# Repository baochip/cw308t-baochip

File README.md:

# Chipwhisperer 308 Target for Baochip

Design files for a chipwhisperer 308 target featuring the Baochip.

Contains a 400MHz bandwidth, 20x amplifier on IDD.

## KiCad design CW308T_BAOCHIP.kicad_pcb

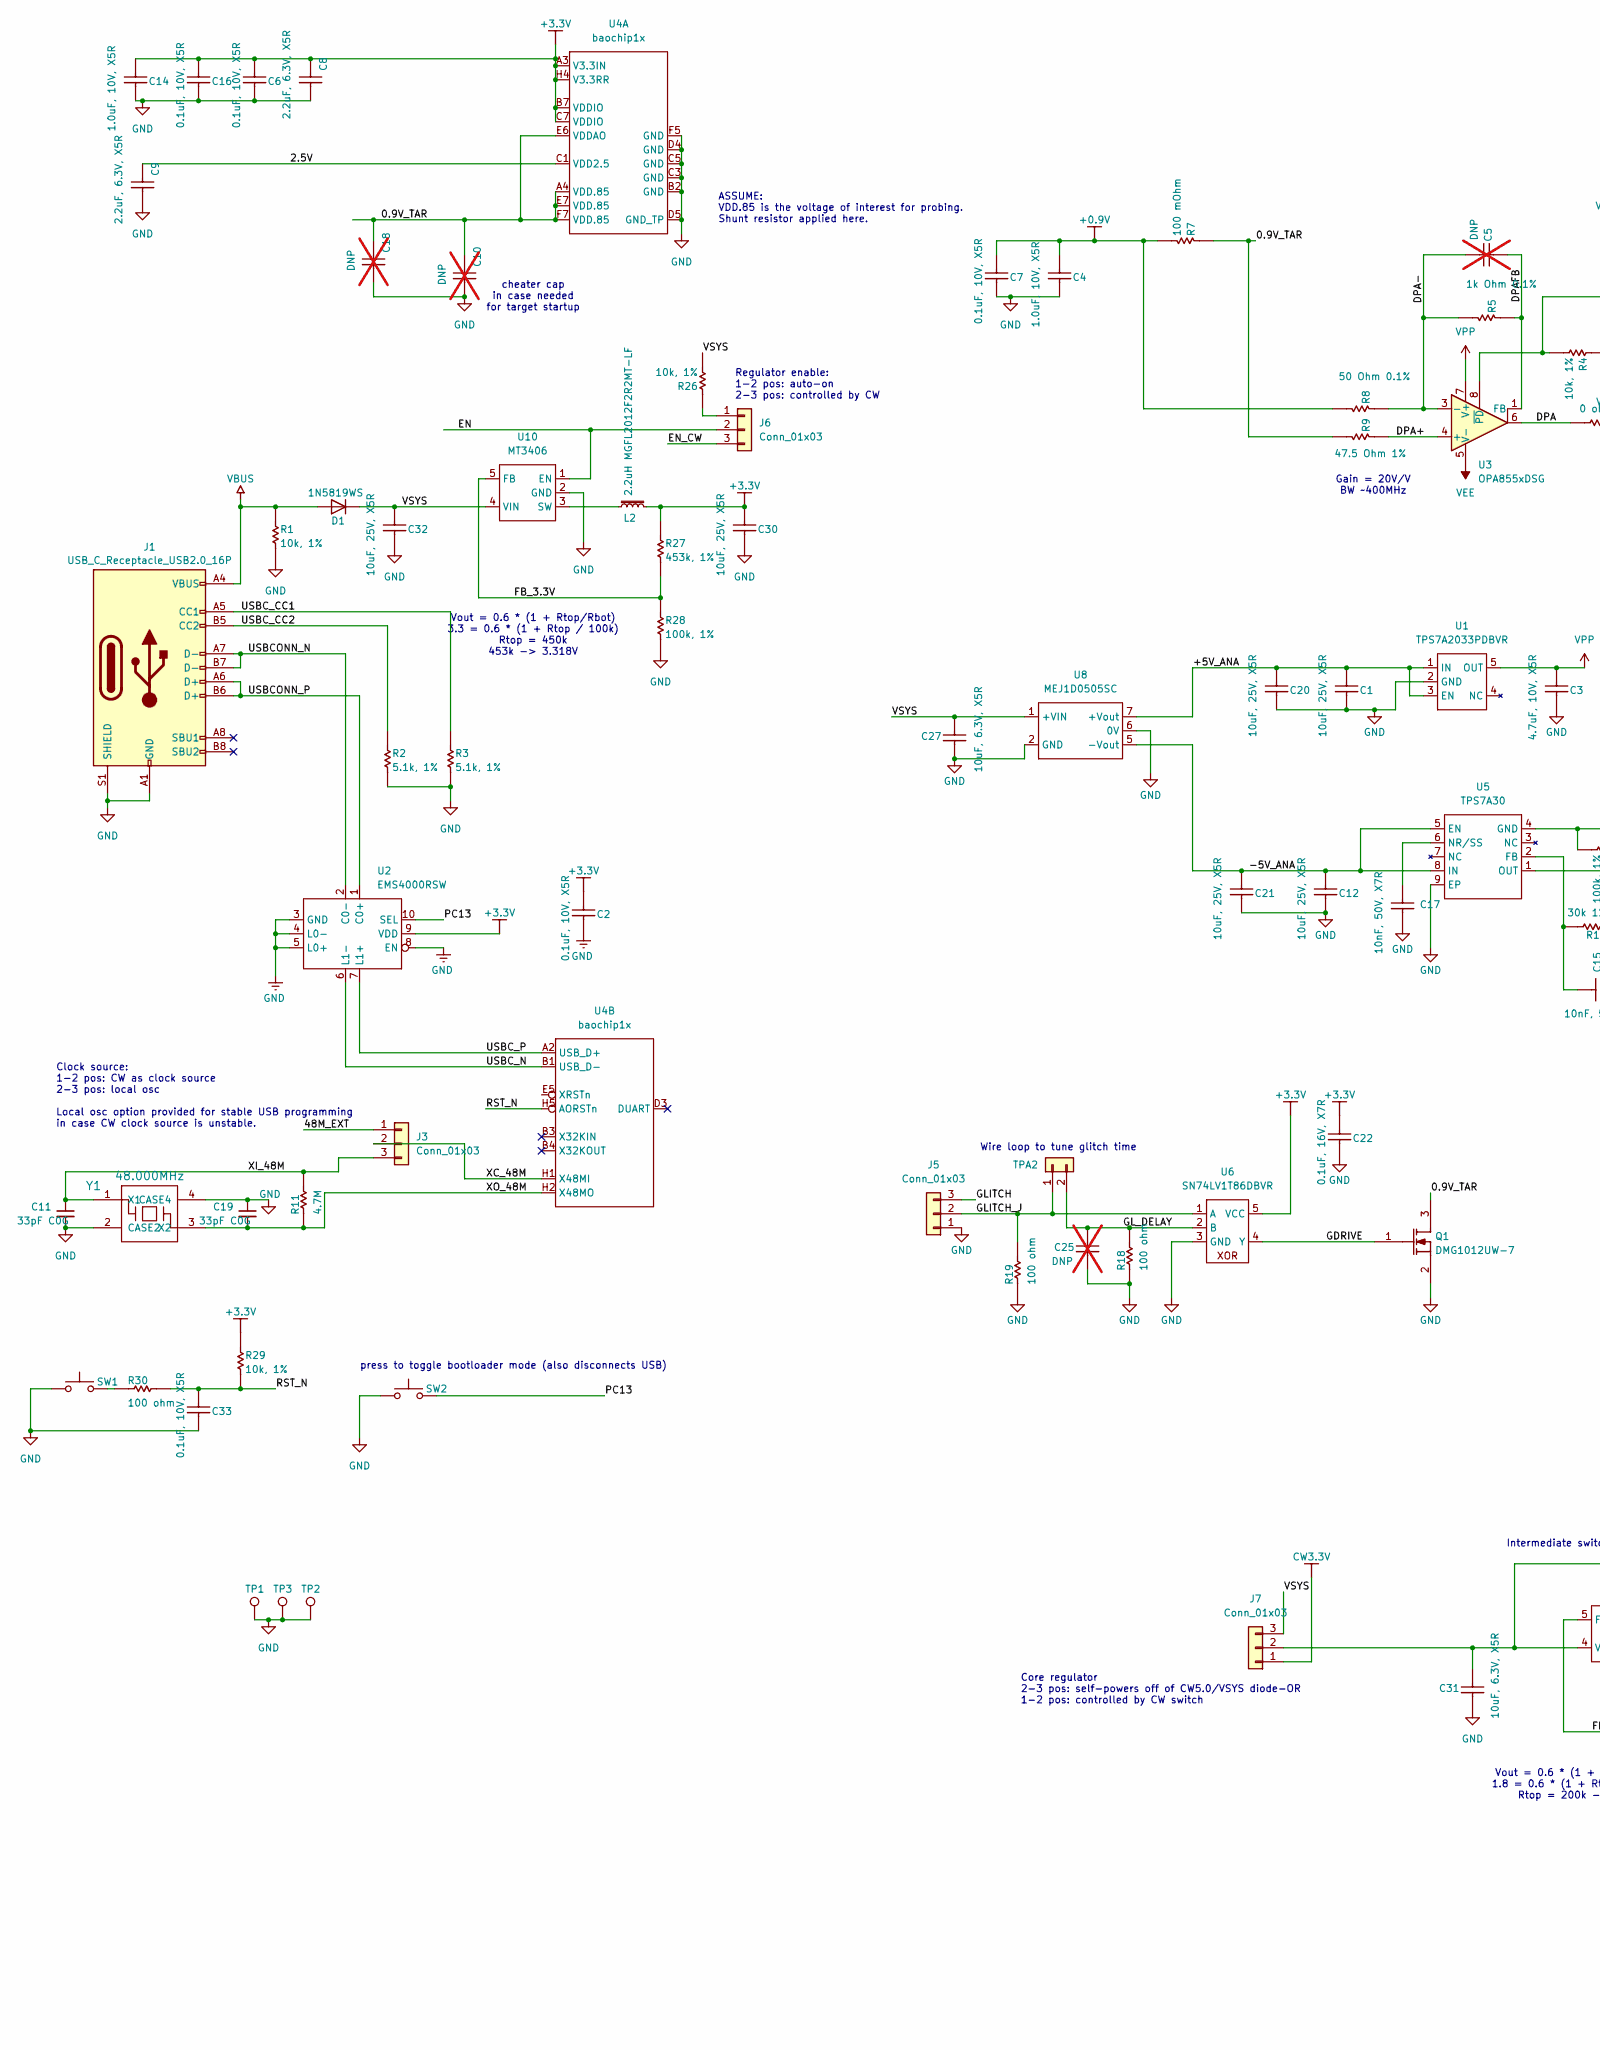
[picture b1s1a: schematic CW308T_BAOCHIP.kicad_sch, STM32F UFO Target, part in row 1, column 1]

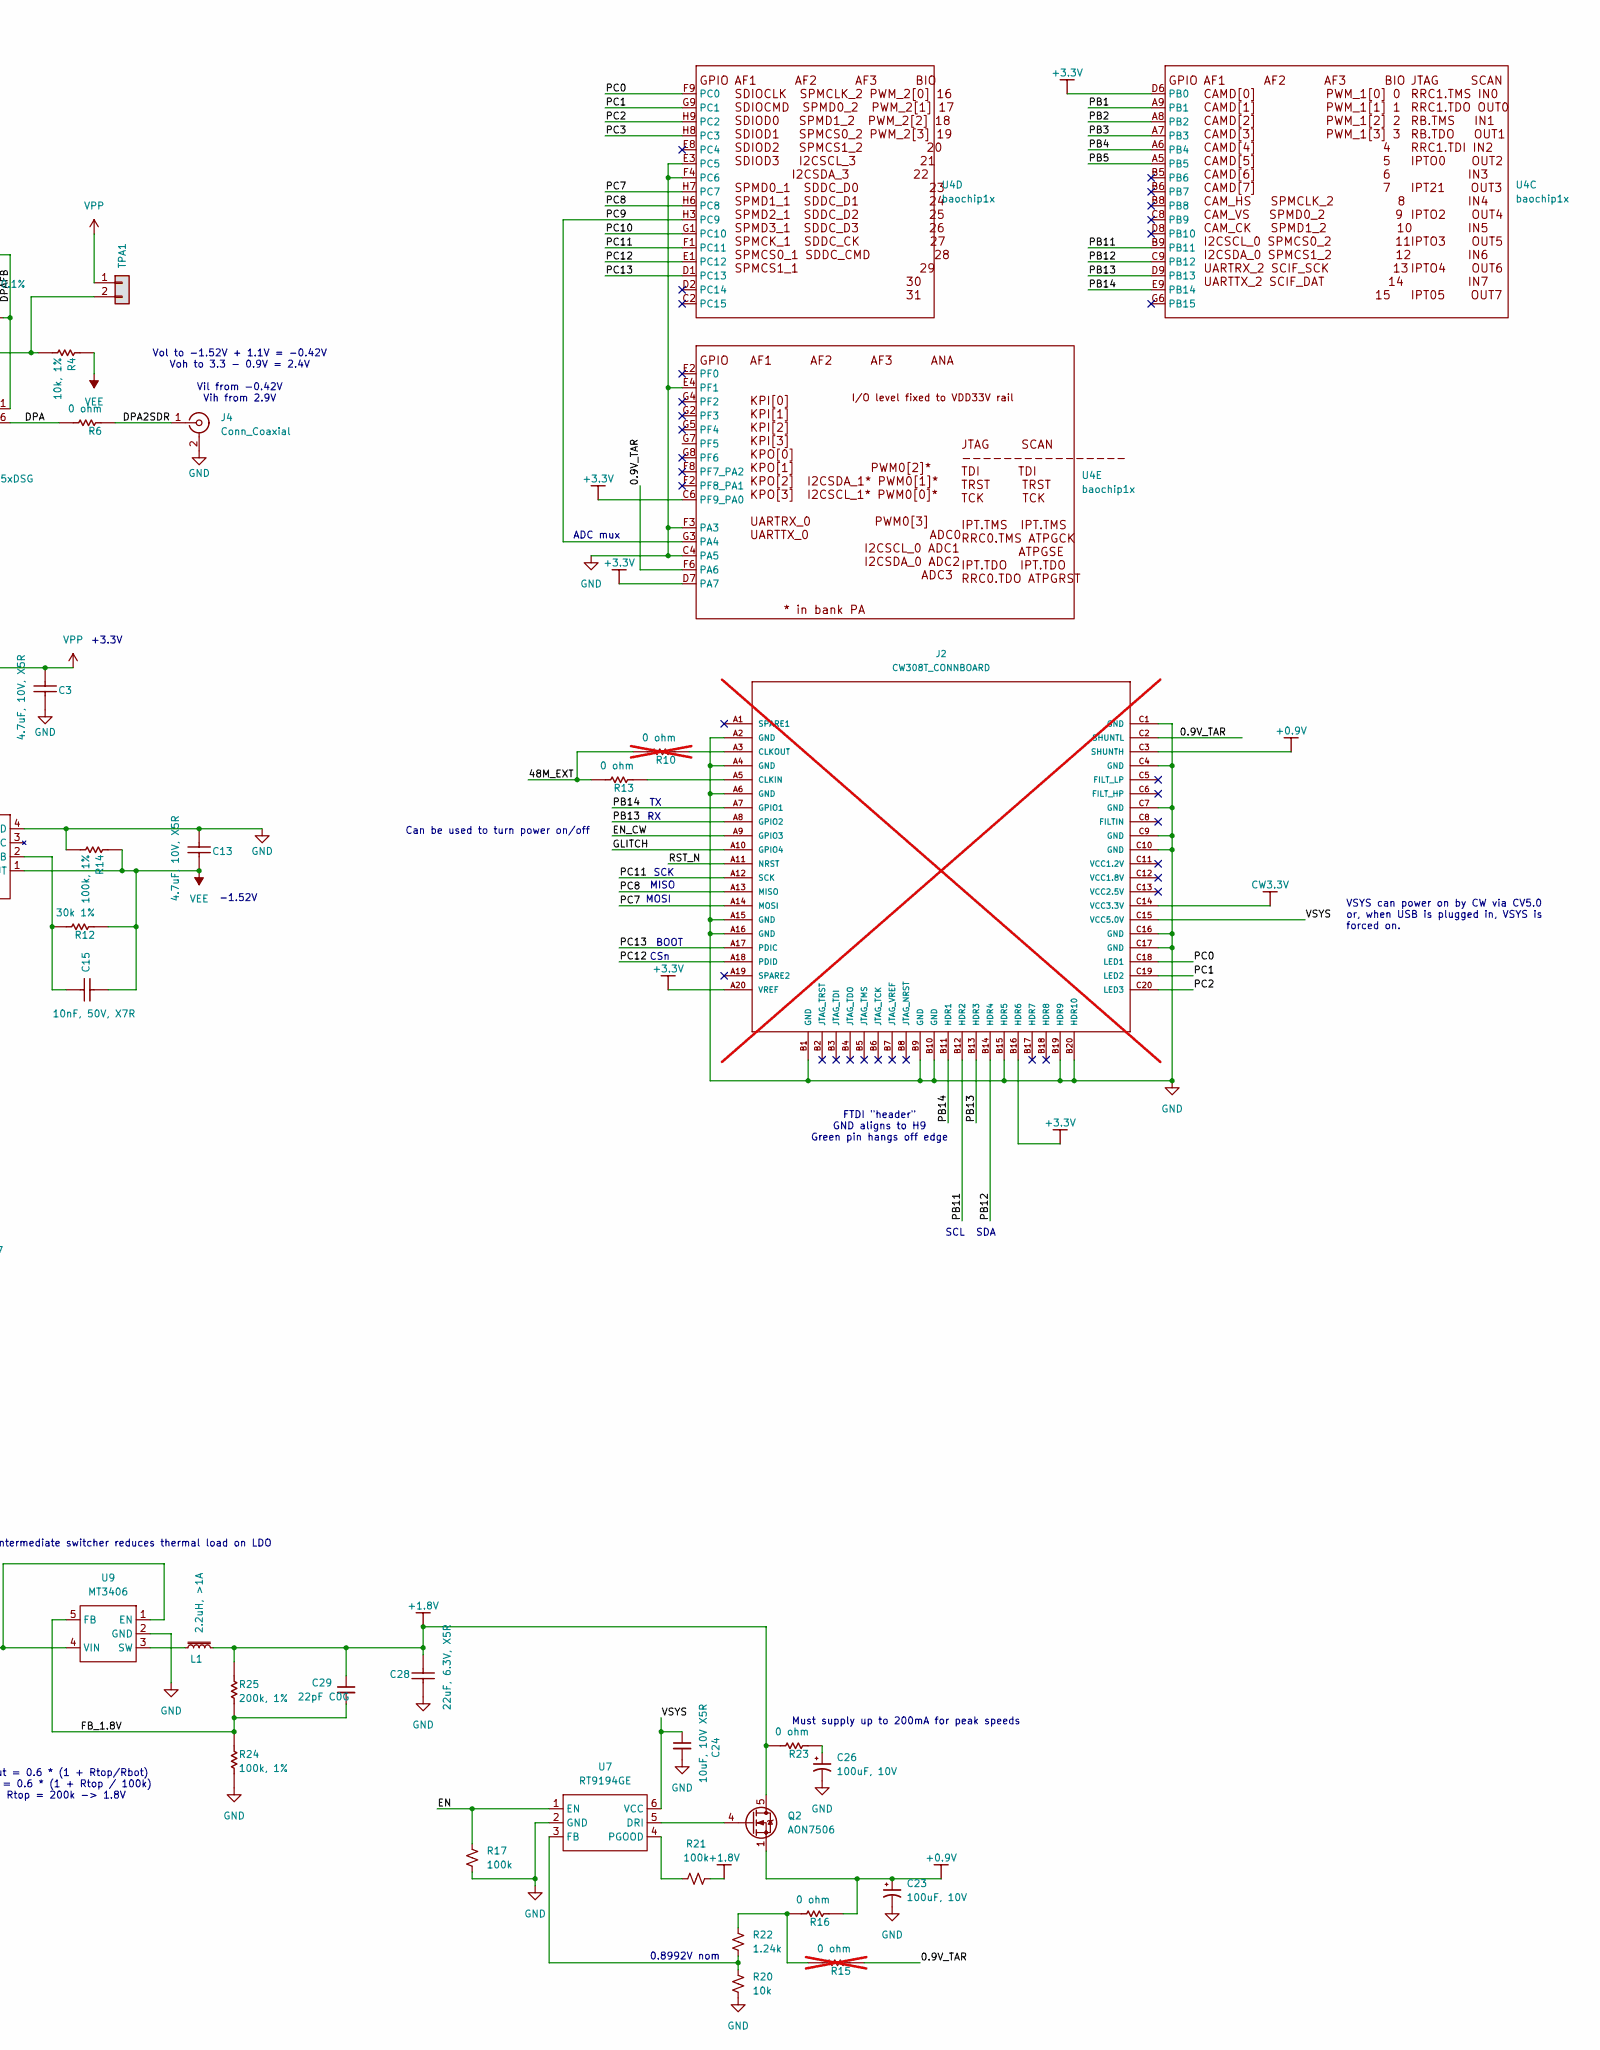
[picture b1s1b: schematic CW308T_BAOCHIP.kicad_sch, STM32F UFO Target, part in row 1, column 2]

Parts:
C1, C12, C20, C21, C30, C32: 10uF, 25V, X5R; C_0603_1608Metric; MPN CL10A106MA8NRNC; LCSC C96446
C2, C6, C7, C16, C33: 0.1uF, 10V, X5R; C_0201_0603Metric; MPN CL05B104KO5NNNC; LCSC C76934
C3, C13: 4.7uF, 10V, X5R; C_0402_1005Metric; MPN CL05A475MP5NRNC; LCSC C23733
C4, C14: 1.0uF, 10V, X5R; C_0201_0603Metric; MPN CL05A105KA5NQNC; LCSC C76935
C5, C25: DNP; C_0402_1005Metric; MPN DNP; LCSC DNP; not fitted
C8, C9: 2.2uF, 6.3V, X5R; C_0201_0603Metric; MPN GRM033R60J225ME47D; LCSC C76933
C10, C18: DNP; C_0402_1005Metric_Pad0.74x0.62mm_HandSolder; LCSC DNP; not fitted
C11, C19: 33pF C0G; C_0201_0603Metric; LCSC C56903
C15, C17: 10nF, 50V, X7R; C_0402_1005Metric; MPN CC0402KRX7R9BB103; LCSC C60133
C22: 0.1uF, 16V, X7R; C_0402_1005Metric; MPN CL05B104KO5NNNC; LCSC C1525
C23, C26: 100uF, 10V; CP_Elec_5x5.4; LCSC C131115
C24: 10uF, 10V X5R; C_0603_1608Metric; LCSC C19702
C27, C31: 10uF, 6.3V, X5R; C_0402_1005Metric; MPN CL05A106MQ5NUNC; LCSC C15525
C28: 22uF, 6.3V, X5R; C_0603_1608Metric; MPN CL10A226MQ8NRNC; LCSC C59461
C29: 22pF C0G; C_0201_0603Metric; Rating C0G 50V 0201; MPN ANY; LCSC C57783
D1: 1N5819WS; D_SOD-323; MPN SD103AWS; LCSC C191023
J1: USB_C_Receptacle_USB2.0_16P; USB_C_Receptacle_HRO_TYPE-C-31-M-12; LCSC C165948
J2: CW308T_CONNBOARD; not fitted
J3, J5, J6, J7: Conn_01x03; PinHeader_1x03_P2.54mm_Vertical; LCSC C2937625
J4: Conn_Coaxial; SMA_Amphenol_901-144_Vertical; LCSC C496549
L1: 2.2uH, >1A; L_0805_2012Metric; LCSC C42455261
L2: 2.2uH MGFL2012F2R2MT-LF; L_0805_2012Metric; LCSC C281115
Q1: DMG1012UW-7; SOT323-3AN; MPN DMG1012UW-7; LCSC C156390
Q2: AON7506; AO_DFN3x3A_8L_EP1_P; LCSC C485678
R1, R26, R29: 10k, 1%; R_0201_0603Metric; MPN ANY; LCSC C106225
R2, R3: 5.1k, 1%; R_0402_1005Metric; MPN ANY; LCSC C25905
R4: 10k, 1%; R_0402_1005Metric; MPN ANY; LCSC C25744
R5: 1k Ohm 0.1%; R_0603_1608Metric_Pad0.98x0.95mm_HandSolder; MPN TBD; LCSC C110776
R6, R13, R16, R23: 0 ohm; R_0402_1005Metric; MPN ANY; LCSC C17168
R7: 100 mOhm; R_0402_1005Metric; MPN TBD; LCSC C270655
R8: 50 Ohm 0.1%; R_0603_1608Metric_Pad0.98x0.95mm_HandSolder; MPN TBD; LCSC C849792
R9: 47.5 Ohm 1%; R_0603_1608Metric_Pad0.98x0.95mm_HandSolder; MPN TBD; LCSC C23062
R10, R15: 0 ohm; R_0402_1005Metric; MPN ANY; LCSC C17168; not fitted
R11: 4.7M; R_0402_1005Metric; MPN ANY; LCSC C474132
R12: 30k 1%; R_0402_1005Metric; MPN ANY; LCSC C138008
R14: 100k, 1%; R_0402_1005Metric; MPN ANY; LCSC C25741
R17, R21: 100k; R_0402_1005Metric; LCSC C60491
R18, R19, R30: 100 ohm; R_0402_1005Metric; MPN ANY; LCSC C106232
R20: 10k; R_0402_1005Metric; LCSC C60490
R22: 1.24k; R_0402_1005Metric; LCSC C274889
R24, R28: 100k, 1%; R_0201_0603Metric; MPN ANY; LCSC C106224
R25: 200k, 1%; R_0201_0603Metric; MPN ANY; LCSC C138163
R27: 453k, 1%; R_0201_0603Metric; MPN ANY; LCSC C423509
SW1, SW2: SW_Push; PANASONIC_EVPAS; MPN EVPAS; LCSC C4365033
TP1, TP2, TP3: TestPoint; TestPoint_Keystone_5015_Micro_Mini; LCSC C3345122
TPA1, TPA2: Conn_01x02; PinHeader_1x02_P2.54mm_Vertical; LCSC C225477
U1: TPS7A2033PDBVR; SOT-23-5; MPN TPS7A2033PDBVR; LCSC C2862740
U2: EMS4000RSW; QFN-10_1.4x1.8_Pitch0.4mm; LCSC C49186227
U3: OPA855xDSG; WSON-8-1EP_2x2mm_P0.5mm_EP0.9x1.6mm; LCSC C2866497
U4: baochip1x; WLCSP-71_9x8_4.062x3.762mm
U5: TPS7A30; HVSSOP-8-1EP_3x3mm_P0.65mm_EP1.57x1.89mm_ThermalVias; MPN TPS7A3001DGNR; LCSC C33835
U6: SN74LV1T86DBVR; SOT-23-5_HandSoldering; MPN SN74LV1T86DBVR; LCSC C2682145
U7: RT9194GE; SOT-23-6; LCSC C17239326
U8: MEJ1D0505SC; MEJ1DxxxxSC; MPN MEJ1D0505SC; LCSC C5369550
U9, U10: MT3406; SOT-23-5; LCSC C22462728
Y1: 48.000MHz; Crystal_SMD_3225-4Pin_3.2x2.5mm; LCSC C2892060

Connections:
+0.9V: C4.1, C7.1, C23.1, J2.C3 (SHUNTH), Q2.1 (S), Q2.2 (S), Q2.3 (S), R7.1, R8.1, R16.1
+1.8V: C28.2, C29.1, L1.2, Q2.5 (D), R21.2, R23.2, R25.1
+3.3V: C2.1, C6.1, C8.1, C14.1, C16.1, C22.1, C30.1, J2.A20 (VREF), J2.B16 (HDR6), L2.2, R27.1, R29.1, U2.9 (VDD), U4.A3 (V3.3IN), U4.B7 (VDDIO), U4.C6 (PF9_PA0), U4.C7 (VDDIO), U4.D6 (PB0), U4.D7 (PA7), U4.H4 (V3.3RR), U6.5 (VCC)
/0.9V_TAR: C10.1, C18.1, J2.C2 (SHUNTL), Q1.3 (D), R7.2, R9.1, R15.1, U4.A4 (VDD.85), U4.E6 (VDDAO), U4.E7 (VDD.85), U4.F6 (PA6), U4.F7 (VDD.85)
/2.5V: C9.1, U4.C1 (VDD2.5)
/48M_EXT: J3.1, R10.2, R13.2
/+5V_ANA: C1.1, C20.1, U1.1 (IN), U1.3 (EN), U8.7 (+Vout)
/-5V_ANA: C12.1, C21.1, U5.5 (EN), U5.8 (IN), U8.5 (-Vout)
/DPA: R6.2, U3.6
/DPA2SDR: J4.1 (In), R6.1
/DPA+: R9.2, U3.4 (+)
/DPA-: C5.1, R5.1, R8.2, U3.3 (-)
/DPAFB: C5.2, R5.2, U3.1 (FB)
/EN: J6.2, R17.2, U7.1 (EN), U10.1 (EN)
/EN_CW: J2.A9 (GPIO3), J6.3
/FB_1.8V: C29.2, R24.1, R25.2, U9.5 (FB)
/FB_3.3V: R27.2, R28.1, U10.5 (FB)
/GDRIVE: Q1.1 (G), U6.4 (Y)
/GLITCH: J2.A10 (GPIO4), J5.3
/GLITCH_J: J5.2, R19.2, TPA2.1, U6.1 (A)
/GL_DELAY: C25.2, R18.2, TPA2.2, U6.2 (B)
/PB1: U4.A9 (PB1)
/PB2: U4.A8 (PB2)
/PB3: U4.A7 (PB3)
/PB4: U4.A6 (PB4)
/PB5: U4.A5 (PB5)
/PB11: J2.B12 (HDR2), U4.B9 (PB11)
/PB12: J2.B14 (HDR4), U4.C9 (PB12)
/PB13: J2.A8 (GPIO2), J2.B13 (HDR3), U4.D9 (PB13)
/PB14: J2.A7 (GPIO1), J2.B11 (HDR1), U4.E9 (PB14)
/PC0: J2.C18 (LED1), U4.F9 (PC0)
/PC1: J2.C19 (LED2), U4.G9 (PC1)
/PC2: J2.C20 (LED3), U4.H9 (PC2)
/PC3: U4.H8 (PC3)
/PC7: J2.A14 (MOSI), U4.H7 (PC7)
/PC8: J2.A13 (MISO), U4.H6 (PC8)
/PC9: U4.G3 (PA4), U4.H3 (PC9)
/PC10: U4.G1 (PC10)
/PC11: J2.A12 (SCK), U4.F1 (PC11)
/PC12: J2.A18 (PDID), U4.E1 (PC12)
/PC13: J2.A17 (PDIC), SW2.2, U2.10 (SEL), U4.D1 (PC13)
/RST_N: C33.1, J2.A11 (NRST), R29.2, R30.2, U4.H5 (AORSTn)
/USBCONN_N: J1.A7 (D-), J1.B7 (D-), U2.2 (C0-)
/USBCONN_P: J1.A6 (D+), J1.B6 (D+), U2.1 (C0+)
/USBC_CC1: J1.A5 (CC1), R3.2
/USBC_CC2: J1.B5 (CC2), R2.2
/USBC_N: U2.6 (L1-), U4.B1 (USB_D-)
/USBC_P: U2.7 (L1+), U4.A2 (USB_D+)
/VSYS: C24.1, C27.2, C32.1, D1.1 (K), J2.C15 (VCC5.0V), J7.3, R26.2, U7.6 (VCC), U8.1 (+VIN), U10.4 (VIN)
/XC_48M: J3.2, U4.H1 (X48MI)
/XI_48M: C11.1, J3.3, R11.2, Y1.1 (X1)
/XO_48M: C19.2, R11.1, U4.H2 (X48MO), Y1.3 (X2)
CW3.3V: J2.C14 (VCC3.3V), J7.1
GND: C1.2, C2.2, C3.2, C4.2, C6.2, C7.2, C8.2, C9.2, C10.2, C11.2, C12.2, C13.1, C14.2, C16.2, C17.2, C18.2, C19.1, C20.2, C21.2, C22.2, C23.2, C24.2, C25.1, C26.2, C27.1, C28.1, C30.2, C31.1, C32.2, C33.2, J1.A1 (GND), J1.A12 (GND), J1.B1 (GND), J1.B12 (GND), J1.S1 (SHIELD), J2.A2 (GND), J2.A4 (GND), J2.A6 (GND), J2.A15 (GND), J2.A16 (GND), J2.B1 (GND), J2.B9 (GND), J2.B10 (GND), J2.B15 (HDR5), J2.B19 (HDR9), J2.B20 (HDR10), J2.C1 (GND), J2.C4 (GND), J2.C7 (GND), J2.C9 (GND), J2.C10 (GND), J2.C16 (GND), J2.C17 (GND), J4.2 (Ext), J5.1, Q1.2 (S), R1.2, R2.1, R3.1, R14.1, R17.1, R18.1, R19.1, R20.2, R24.2, R28.2, SW1.1, SW2.1, TP1.1 (1_1), TP2.1 (1_1), TP3.1 (1_1), U1.2 (GND), U2.3 (GND), U2.4 (L0-), U2.5 (L0+), U2.8 (EN), U4.B2 (GND), U4.C3 (GND), U4.C4 (PA5), U4.C5 (GND), U4.D4 (GND), U4.D5 (GND_TP), U4.E3 (PC5), U4.E4 (PF1), U4.F3 (PA3), U4.F4 (PC6), U4.F5 (GND), U5.4 (GND), U5.9 (EP), U6.3 (GND), U7.2 (GND), U8.2 (GND), U8.6 (0V), U9.2 (GND), U10.2 (GND), Y1.2 (CASE2), Y1.4 (CASE4)
unnamed: C26.1, R23.1
unnamed: J2.A5 (CLKIN), R13.1
unnamed: J2.A3 (CLKOUT), R10.1
unnamed: J6.1, R26.1
unnamed: C31.2, J7.2, U9.1 (EN), U9.4 (VIN)
unnamed: Q2.4 (G), U7.5 (DRI)
unnamed: R15.2, R16.2, R22.1
unnamed: R30.1, SW1.2
unnamed: R4.2, TPA1.2, U3.8 (~PD)
unnamed: C15.1, R12.2, U5.2 (FB)
unnamed: C17.1, U5.6 (NR/SS)
unnamed: R20.1, R22.2, U7.3 (FB)
unnamed: R21.1, U7.4 (PGOOD)
unnamed: L1.1, U9.3 (SW)
unnamed: L2.1, U10.3 (SW)
VBUS: D1.2 (A), J1.A4 (VBUS), J1.A9 (VBUS), J1.B4 (VBUS), J1.B9 (VBUS), R1.1
VEE: C13.2, C15.2, R4.1, R12.1, R14.2, U3.5 (V-), U3.9 (V-), U5.1 (OUT)
VPP: C3.1, TPA1.1, U1.5 (OUT), U3.7 (V+)

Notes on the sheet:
SCK
press to toggle bootloader mode (also disconnects USB)
0.8992V nom
Vout = 0.6 * (1 + Rtop/Rbot) 1.8 = 0.6 * (1 + Rtop / 100k) Rtop = 200k -> 1.8V
Core regulator 2-3 pos: self-powers off of CW5.0/VSYS diode-OR 1-2 pos: controlled by CW switch
+3.3V
Must supply up to 200mA for peak speeds
Wire loop to tune glitch time
Gain = 20V/V BW ~400MHz
Regulator enable: 1-2 pos: auto-on 2-3 pos: controlled by CW
Vout = 0.6 * (1 + Rtop/Rbot) 3.3 = 0.6 * (1 + Rtop / 100k) Rtop = 450k 453k -> 3.318V
MISO
VSYS can power on by CW via CV5.0 or, when USB is plugged in, VSYS is forced on.
Clock source: 1-2 pos: CW as clock source 2-3 pos: local osc Local osc option provided for stable USB programming in case CW clock source is unstable.
cheater cap in case needed for target startup
ASSUME: VDD.85 is the voltage of interest for probing. Shunt resistor applied here.
BOOT
Can be used to turn power on/off
Intermediate switcher reduces thermal load on LDO
Vol to -1.52V + 1.1V = -0.42V Voh to 3.3 - 0.9V = 2.4V Vil from -0.42V Vih from 2.9V
ADC mux
MOSI
FTDI "header" GND aligns to H9 Green pin hangs off edge
SDA
-1.52V
SCL
CSn

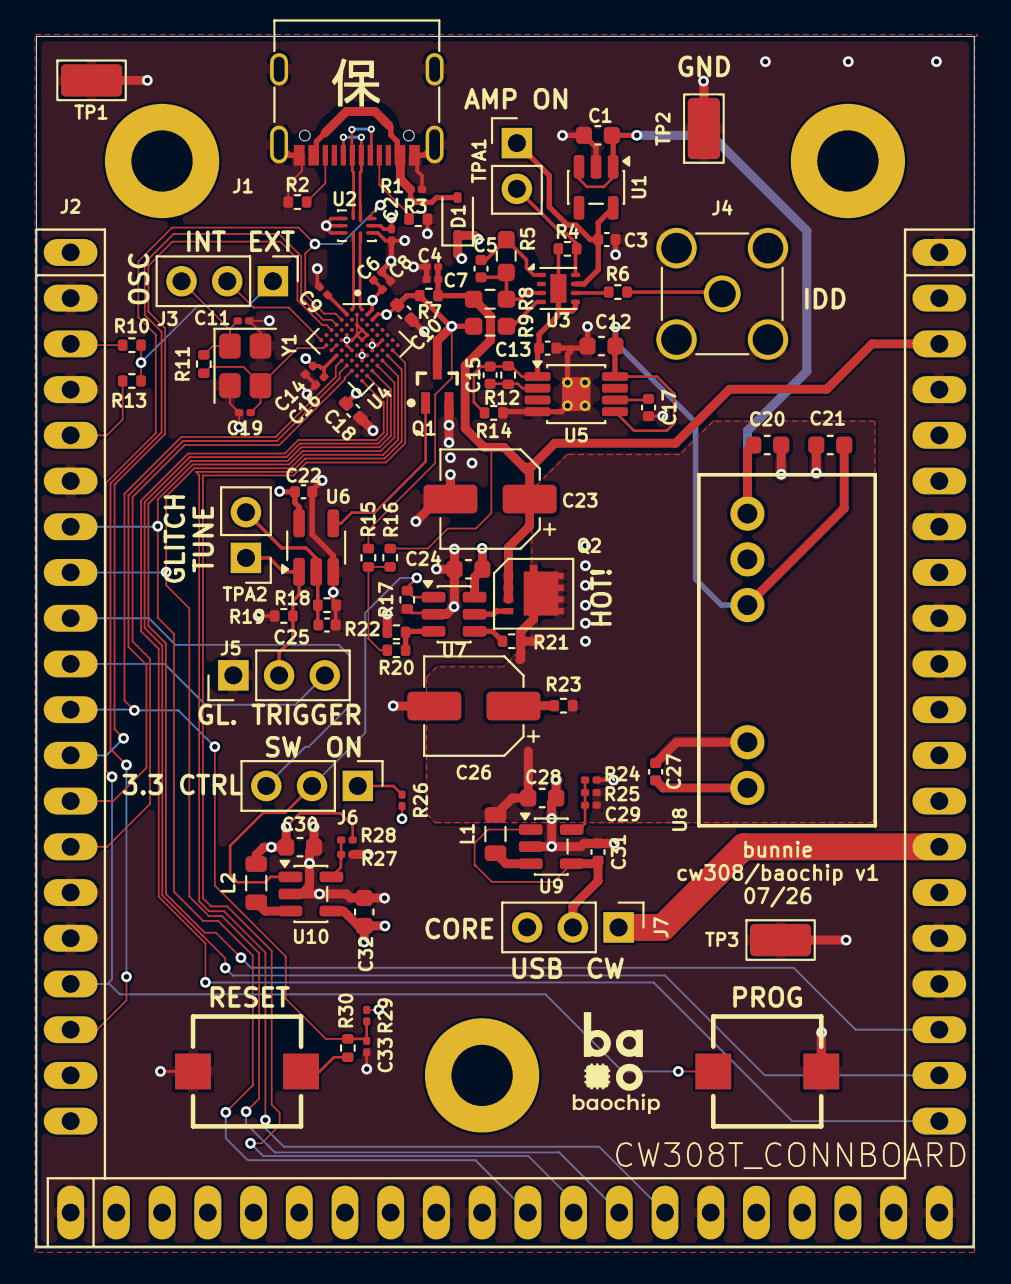
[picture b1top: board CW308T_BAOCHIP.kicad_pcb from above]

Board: 4 copper layers, 52.1 x 67.3 mm, 93 parts (0 on the bottom side), 65 nets.
